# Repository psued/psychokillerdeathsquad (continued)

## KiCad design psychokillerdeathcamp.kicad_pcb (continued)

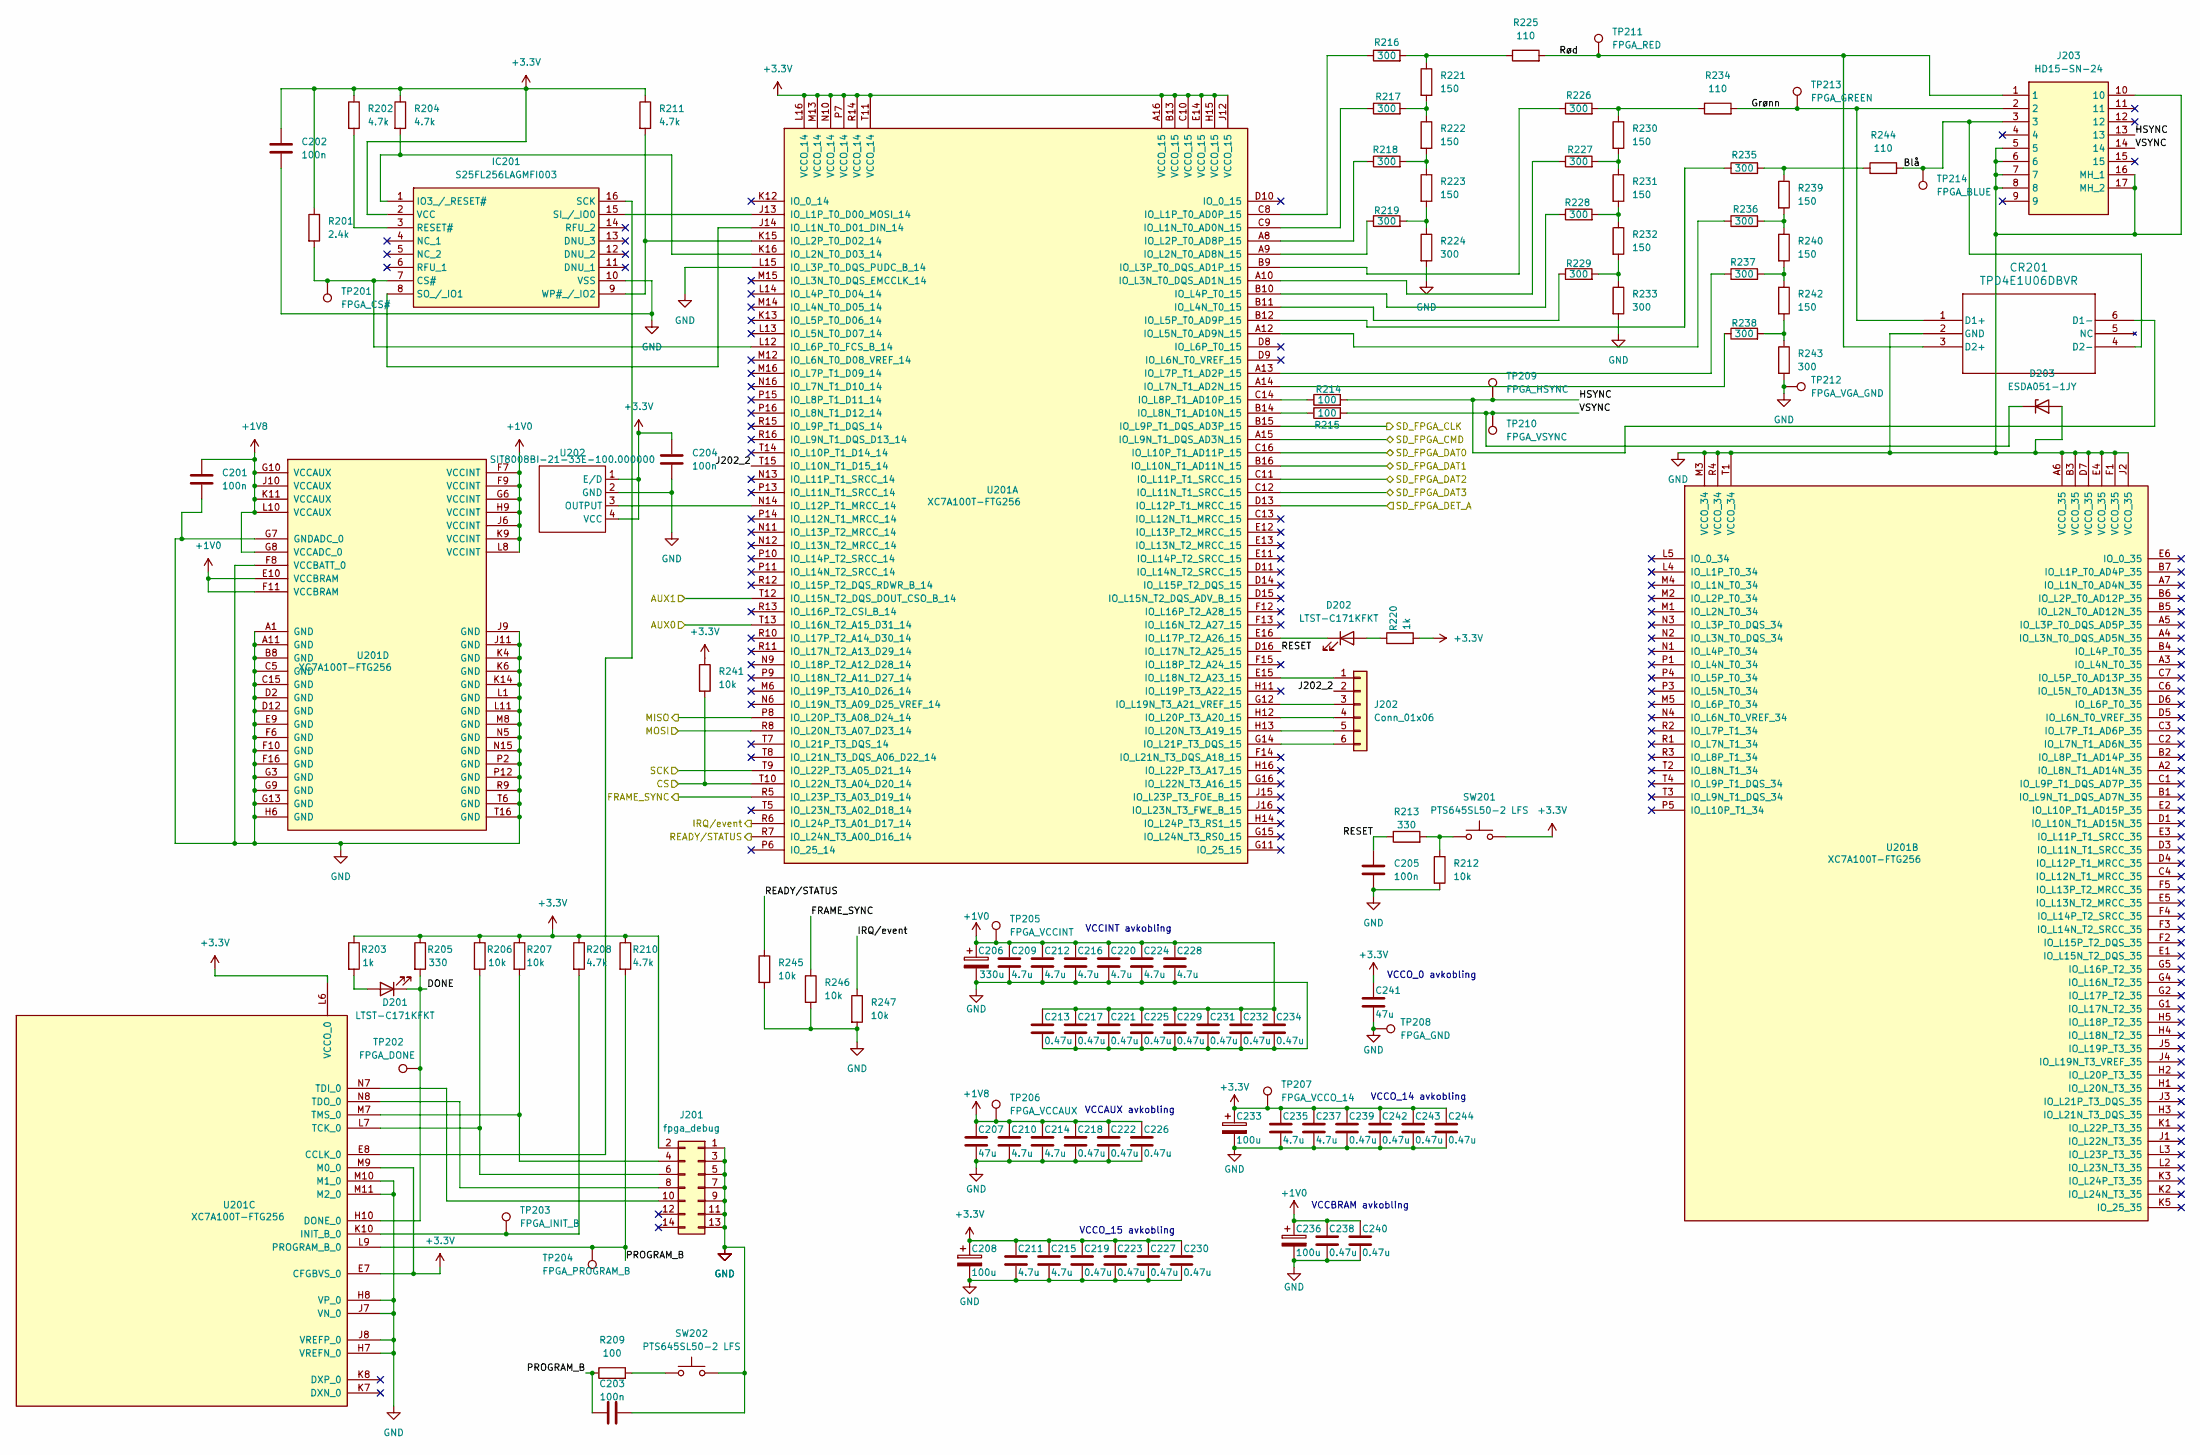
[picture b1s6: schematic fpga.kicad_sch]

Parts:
C201, C202, C203, C204, C205: 100n; C_0805_2012Metric_Pad1.18x1.45mm_HandSolder
C206: 330u; CP_EIA-7343-20_Kemet-V_HandSolder
C207, C241: 47u; C_1210_3225Metric_Pad1.33x2.70mm_HandSolder
C208, C233, C236: 100u; CP_EIA-3216-18_Kemet-A_HandSolder
C209, C210, C211, C212, C214, C215, C216, C220, C224, C228, C235, C237: 4.7u; C_0805_2012Metric_Pad1.18x1.45mm_HandSolder
C213, C217, C218, C219, C221, C222, C223, C225, C226, C227, C229, C230, C231, C232, C234, C238, C239, C240, C242, C243, C244: 0.47u; C_0805_2012Metric_Pad1.18x1.45mm_HandSolder
CR201: TPD4E1U06DBVR
D201, D202: LTST-C171KFKT; LED_0805_2012Metric_Pad1.15x1.40mm_HandSolder
D203: ESDA051-1JY; D_SOD-323_HandSoldering
IC201: S25FL256LAGMFI003; SOIC-16W_7.5x10.3mm_P1.27mm; Mouser Part Number 727-S25FL256LAGMFI03
J201: fpga_debug; SHDR14W55P200_2X7_1665X630X640P
J202: Conn_01x06; PinHeader_1x06_P2.54mm_Vertical
J203: HD15-SN-24; HD15SN24; Manufacturer_Part_Number HD15-SN-24
R201: 2.4k; R_0805_2012Metric_Pad1.20x1.40mm_HandSolder
R202, R204, R208, R210, R211: 4.7k; R_0805_2012Metric_Pad1.20x1.40mm_HandSolder
R203, R220: 1k; R_0805_2012Metric_Pad1.20x1.40mm_HandSolder
R205, R213: 330; R_0805_2012Metric_Pad1.20x1.40mm_HandSolder
R206, R207, R212, R241, R245, R246, R247: 10k; R_0805_2012Metric_Pad1.20x1.40mm_HandSolder
R209, R214, R215: 100; R_0805_2012Metric_Pad1.20x1.40mm_HandSolder
R216, R217, R218, R219, R224, R226, R227, R228, R229, R233, R235, R236, R237, R238, R243: 300; R_0805_2012Metric_Pad1.20x1.40mm_HandSolder
R221, R222, R223, R230, R231, R232, R239, R240, R242: 150; R_0805_2012Metric_Pad1.20x1.40mm_HandSolder
R225, R234, R244: 110; R_0805_2012Metric_Pad1.20x1.40mm_HandSolder
SW201, SW202: PTS645SL50-2 LFS; SW_PUSH_6mm_H5mm
TP201: FPGA_CS#; TestPoint_Pad_D1.5mm
TP202: FPGA_DONE; TestPoint_Pad_D1.5mm
TP203: FPGA_INIT_B; PinHeader_1x01_P2.54mm_Vertical
TP204: FPGA_PROGRAM_B; TestPoint_Pad_D1.5mm
TP205: FPGA_VCCINT; TestPoint_Pad_D1.5mm
TP206: FPGA_VCCAUX; TestPoint_Pad_D1.5mm
TP207: FPGA_VCCO_14; TestPoint_Pad_D1.5mm
TP208: FPGA_GND; PinHeader_1x01_P2.54mm_Vertical
TP209: FPGA_HSYNC; TestPoint_Pad_D1.5mm
TP210: FPGA_VSYNC; TestPoint_Pad_D1.5mm
TP211: FPGA_RED; TestPoint_Pad_D1.5mm
TP212: FPGA_VGA_GND; PinHeader_1x01_P2.54mm_Vertical
TP213: FPGA_GREEN; TestPoint_Pad_D1.5mm
TP214: FPGA_BLUE; TestPoint_Pad_D1.5mm
U201: XC7A100T-FTG256; BGA-256_17.0x17.0mm_Layout16x16_P1.0mm_Ball0.5mm_Pad0.4mm_N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
U202: SIT8008BI-21-33E-100.000000; OSC_SiT8008BI-21-33E-100.000000

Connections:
+1V0: C206.1, C209.1, C212.1, C213.1, C216.1, C217.1, C220.1, C221.1, C224.1, C225.1, C228.1, C229.1, C231.1, C232.1, C234.1, C236.1, C238.1, C240.1, TP205.1 (1_1), U201.E10 (VCCBRAM), U201.F7 (VCCINT), U201.F9 (VCCINT), U201.F11 (VCCBRAM), U201.G6 (VCCINT), U201.H9 (VCCINT), U201.J6 (VCCINT), U201.K9 (VCCINT), U201.L8 (VCCINT); also elsewhere on the board
+1V8: C201.1, C207.1, C210.1, C214.1, C218.1, C222.1, C226.1, TP206.1 (1_1), U201.G8 (VCCADC_0), U201.G10 (VCCAUX), U201.J10 (VCCAUX), U201.K11 (VCCAUX), U201.L10 (VCCAUX); also elsewhere on the board
+3.3V: C202.1, C204.1, C208.1, C211.1, C215.1, C219.1, C223.1, C227.1, C230.1, C233.1, C235.1, C237.1, C239.1, C241.1, C242.1, C243.1, C244.1, IC201.2 (VCC), J201.2, R201.1, R202.1, R203.1, R204.1, R205.1, R206.1, R207.1, R208.1, R210.1, R211.1, R220.2, R241.1, SW201.2, TP207.1 (1_1), U201.A16 (VCCO_15), U201.B13 (VCCO_15), U201.C10 (VCCO_15), U201.E7 (CFGBVS_0), U201.E14 (VCCO_15), U201.H15 (VCCO_15), U201.J12 (VCCO_15), U201.L6 (VCCO_0), U201.L16 (VCCO_14), U201.M9 (M0_0), U201.M13 (VCCO_14), U201.N10 (VCCO_14), U201.P7 (VCCO_14), U201.R14 (VCCO_14), U201.T11 (VCCO_14), U202.1 (E/D), U202.4 (VCC); also elsewhere on the board
/MCU/AUX0: U201.T13 (IO_L16N_T2_A15_D31_14); also elsewhere on the board
/MCU/AUX1: U201.T12 (IO_L15N_T2_DQS_DOUT_CSO_B_14); also elsewhere on the board
/MCU/CS: R241.2, U201.T10 (IO_L22N_T3_A04_D20_14); also elsewhere on the board
/MCU/MISO: U201.P8 (IO_L20P_T3_A08_D24_14); also elsewhere on the board
/MCU/MOSI: U201.R8 (IO_L20N_T3_A07_D23_14); also elsewhere on the board
/MCU/SCK: U201.T9 (IO_L22P_T3_A05_D21_14); also elsewhere on the board
/SD cards/SD_FPGA_CLK: U201.B15 (IO_L9P_T1_DQS_AD3P_15); also elsewhere on the board
/SD cards/SD_FPGA_CMD: U201.A15 (IO_L9N_T1_DQS_AD3N_15); also elsewhere on the board
/SD cards/SD_FPGA_DAT0: U201.C16 (IO_L10P_T1_AD11P_15); also elsewhere on the board
/SD cards/SD_FPGA_DAT1: U201.B16 (IO_L10N_T1_AD11N_15); also elsewhere on the board
/SD cards/SD_FPGA_DAT2: U201.C11 (IO_L11P_T1_SRCC_15); also elsewhere on the board
/SD cards/SD_FPGA_DAT3: U201.C12 (IO_L11N_T1_SRCC_15); also elsewhere on the board
/SD cards/SD_FPGA_DET_A: U201.D13 (IO_L12P_T1_MRCC_15); also elsewhere on the board
/fpga/Blå: CR201.4 (D2-), J203.3, R244.2, TP214.1 (1_1)
/fpga/DONE: D201.1 (K), R205.2, TP202.1 (1_1), U201.H10 (DONE_0)
/fpga/FRAME_SYNC: R246.1, U201.R5 (IO_L23P_T3_A03_D19_14); also elsewhere on the board
/fpga/Grønn: CR201.1 (D1+), J203.2, R234.2, TP213.1 (1_1)
/fpga/HSYNC: CR201.6 (D1-), J203.13, R214.2, TP209.1 (1_1)
/fpga/IRQ/event: R247.1, U201.R6 (IO_L24P_T3_A01_D17_14); also elsewhere on the board
/fpga/J202_2: J202.2, U201.T15 (IO_L10N_T1_D15_14)
/fpga/PROGRAM_B: C203.2, R209.1, R210.2, TP204.1 (1_1), U201.L9 (PROGRAM_B_0)
/fpga/READY/STATUS: R245.1, U201.R7 (IO_L24N_T3_A00_D16_14); also elsewhere on the board
/fpga/RESET: C205.1, R213.1, U201.D16 (IO_L17N_T2_A25_15)
/fpga/Rød: CR201.3 (D2+), J203.1, R225.2, TP211.1 (1_1)
/fpga/VSYNC: D203.1 (K), J203.14, R215.2, TP210.1 (1_1)
GND: C201.2, C202.2, C203.1, C204.2, C205.2, C206.2, C207.2, C208.2, C209.2, C210.2, C211.2, C212.2, C213.2, C214.2, C215.2, C216.2, C217.2, C218.2, C219.2, C220.2, C221.2, C222.2, C223.2, C224.2, C225.2, C226.2, C227.2, C228.2, C229.2, C230.2, C231.2, C232.2, C233.2, C234.2, C235.2, C236.2, C237.2, C238.2, C239.2, C240.2, C241.2, C242.2, C243.2, C244.2, CR201.2 (GND), D203.2 (A), IC201.10 (VSS), J201.1, J201.3, J201.5, J201.7, J201.9, J201.11, J201.13, J203.5, J203.6, J203.7, J203.8, J203.10, J203.16 (MH_1), J203.17 (MH_2), R212.2, R224.2, R233.2, R243.2, R245.2, R246.2, R247.2, SW202.2, TP208.1 (1_1), TP212.1 (1_1), U201.A1 (GND), U201.A6 (VCCO_35), U201.A11 (GND), U201.B3 (VCCO_35), U201.B8 (GND), U201.C5 (GND), U201.C15 (GND), U201.D2 (GND), U201.D7 (VCCO_35), U201.D12 (GND), U201.E4 (VCCO_35), U201.E9 (GND), U201.F1 (VCCO_35), U201.F6 (GND), U201.F8 (VCCBATT_0), U201.F10 (GND), U201.F16 (GND), U201.G3 (GND), U201.G7 (GNDADC_0), U201.G9 (GND), U201.G13 (GND), U201.H6 (GND), U201.H7 (VREFN_0), U201.H8 (VP_0), U201.J2 (VCCO_35), U201.J7 (VN_0), U201.J8 (VREFP_0), U201.J9 (GND), U201.J11 (GND), U201.K4 (GND), U201.K6 (GND), U201.K14 (GND), U201.L1 (GND), U201.L11 (GND), U201.L15 (IO_L3P_T0_DQS_PUDC_B_14), U201.M3 (VCCO_34), U201.M8 (GND), U201.M10 (M1_0), U201.M11 (M2_0), U201.N5 (GND), U201.N15 (GND), U201.P2 (GND), U201.P12 (GND), U201.R4 (VCCO_34), U201.R9 (GND), U201.T1 (VCCO_34), U201.T6 (GND), U201.T16 (GND), U202.2 (GND); also elsewhere on the board
unnamed: D201.2 (A), R203.2
unnamed: D202.2 (A), R220.1
unnamed: D202.1 (K), U201.E16 (IO_L17P_T2_A26_15)
unnamed: IC201.7 (CS#), R201.2, TP201.1 (1_1), U201.L12 (IO_L6P_T0_FCS_B_14)
unnamed: IC201.1 (IO3_/_RESET#), R204.2, U201.K16 (IO_L2N_T0_D03_14)
unnamed: IC201.3 (RESET#), R202.2
unnamed: IC201.16 (SCK), U201.E8 (CCLK_0)
unnamed: IC201.15 (SI_/_IO0), U201.J13 (IO_L1P_T0_D00_MOSI_14)
unnamed: IC201.8 (SO_/_IO1), U201.J14 (IO_L1N_T0_D01_DIN_14)
unnamed: IC201.9 (WP#_/_IO2), R211.2, U201.K15 (IO_L2P_T0_D02_14)
unnamed: J201.4, R207.2, U201.M7 (TMS_0)
unnamed: J201.6, R206.2, U201.L7 (TCK_0)
unnamed: J201.8, U201.N8 (TDO_0)
unnamed: J201.10, U201.N7 (TDI_0)
unnamed: J202.1, U201.E15 (IO_L18N_T2_A23_15)
unnamed: J202.3, U201.G12 (IO_L19N_T3_A21_VREF_15)
unnamed: J202.4, U201.H12 (IO_L20P_T3_A20_15)
unnamed: J202.5, U201.H13 (IO_L20N_T3_A19_15)
unnamed: J202.6, U201.G14 (IO_L21P_T3_DQS_15)
unnamed: R209.2, SW202.1
unnamed: R212.1, R213.2, SW201.1
unnamed: R216.2, R221.1, R225.1
unnamed: R217.2, R221.2, R222.1
unnamed: R218.2, R222.2, R223.1
unnamed: R219.2, R223.2, R224.1
unnamed: R226.2, R230.1, R234.1
unnamed: R227.2, R230.2, R231.1
unnamed: R228.2, R231.2, R232.1
unnamed: R229.2, R232.2, R233.1
unnamed: R235.2, R239.1, R244.1
unnamed: R236.2, R239.2, R240.1
unnamed: R237.2, R240.2, R242.1
unnamed: R238.2, R242.2, R243.1
unnamed: R217.1, U201.C9 (IO_L1N_T0_AD0N_15)
unnamed: R216.1, U201.C8 (IO_L1P_T0_AD0P_15)
unnamed: R219.1, U201.A9 (IO_L2N_T0_AD8N_15)
unnamed: R218.1, U201.A8 (IO_L2P_T0_AD8P_15)
unnamed: R227.1, U201.A10 (IO_L3N_T0_DQS_AD1N_15)
unnamed: R226.1, U201.B9 (IO_L3P_T0_DQS_AD1P_15)
unnamed: R229.1, U201.B11 (IO_L4N_T0_15)
unnamed: R228.1, U201.B10 (IO_L4P_T0_15)
unnamed: R236.1, U201.A12 (IO_L5N_T0_AD9N_15)
unnamed: R235.1, U201.B12 (IO_L5P_T0_AD9P_15)
unnamed: R238.1, U201.A14 (IO_L7N_T1_AD2N_15)
unnamed: R237.1, U201.A13 (IO_L7P_T1_AD2P_15)
unnamed: R215.1, U201.B14 (IO_L8N_T1_AD10N_15)
unnamed: R214.1, U201.C14 (IO_L8P_T1_AD10P_15)
unnamed: U201.N14 (IO_L12P_T1_MRCC_14), U202.3 (OUTPUT)
unnamed: R208.2, TP203.1 (1_1), U201.K10 (INIT_B_0)

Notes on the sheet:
VCCAUX avkobling
VCCO_15 avkobling
VCCO_0 avkobling
VCCBRAM avkobling
VCCO_14 avkobling
VCCINT avkobling

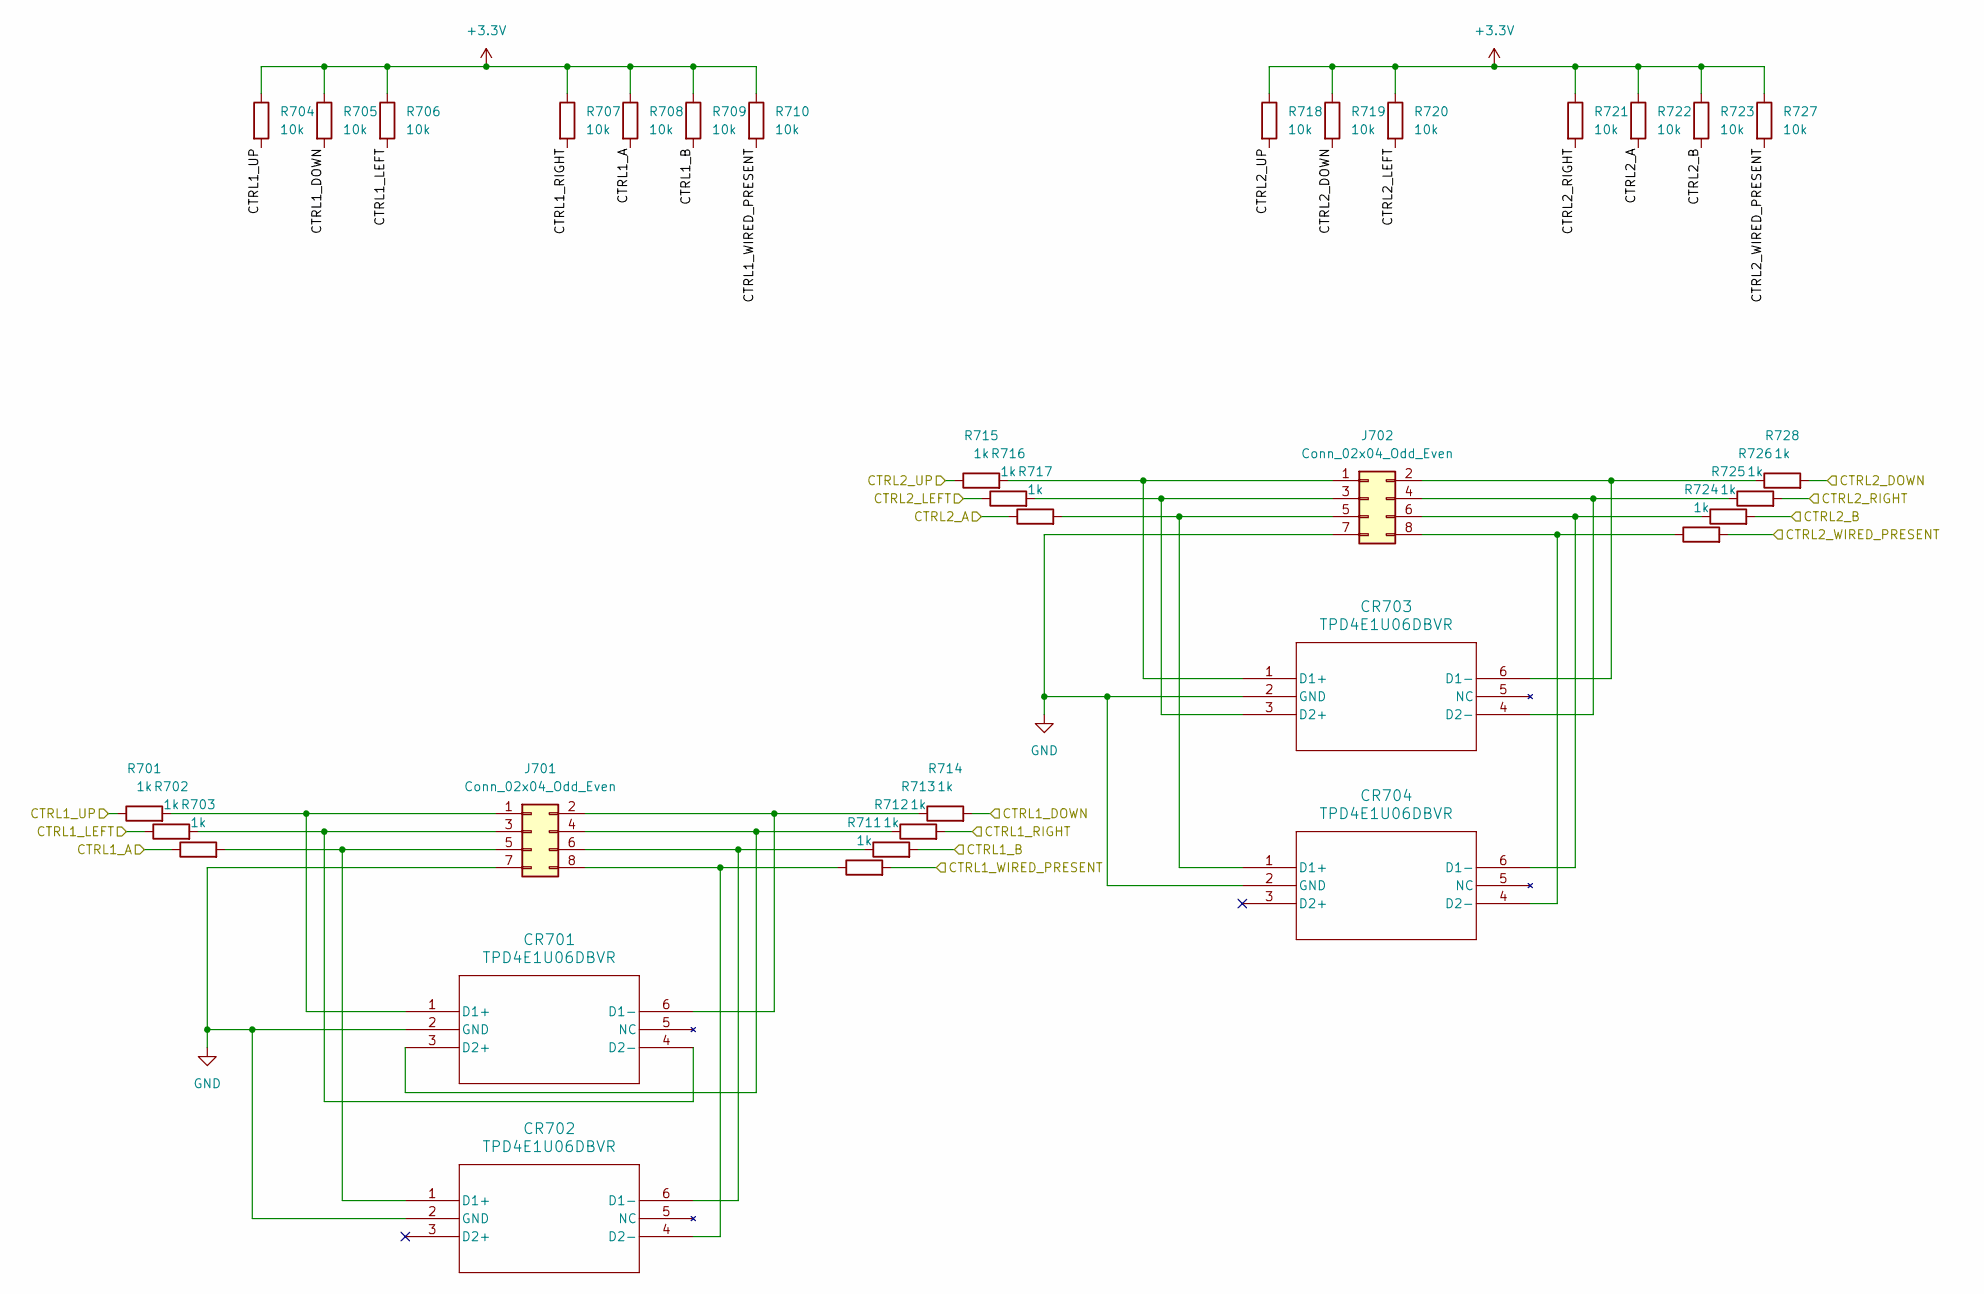
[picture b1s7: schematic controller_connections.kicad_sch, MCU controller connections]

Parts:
CR701, CR702, CR703, CR704: TPD4E1U06DBVR
J701, J702: Conn_02x04_Odd_Even; Molex_Micro-Fit_3.0_43045-0800_2x04_P3.00mm_Horizontal
R701, R702, R703, R711, R712, R713, R714, R715, R716, R717, R724, R725, R726, R728: 1k; R_0805_2012Metric_Pad1.20x1.40mm_HandSolder
R704, R705, R706, R707, R708, R709, R710, R718, R719, R720, R721, R722, R723, R727: 10k; R_0805_2012Metric_Pad1.20x1.40mm_HandSolder

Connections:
+3.3V: R704.1, R705.1, R706.1, R707.1, R708.1, R709.1, R710.1, R718.1, R719.1, R720.1, R721.1, R722.1, R723.1, R727.1; also elsewhere on the board
/MCU/Controller connections/CTRL1_A: R703.1, R708.2; also elsewhere on the board
/MCU/Controller connections/CTRL1_B: R709.2, R712.2; also elsewhere on the board
/MCU/Controller connections/CTRL1_DOWN: R705.2, R714.2; also elsewhere on the board
/MCU/Controller connections/CTRL1_LEFT: R702.1, R706.2; also elsewhere on the board
/MCU/Controller connections/CTRL1_RIGHT: R707.2, R713.2; also elsewhere on the board
/MCU/Controller connections/CTRL1_UP: R701.1, R704.2; also elsewhere on the board
/MCU/Controller connections/CTRL1_WIRED_PRESENT: R710.2, R711.2; also elsewhere on the board
/MCU/Controller connections/CTRL2_A: R717.1, R722.2; also elsewhere on the board
/MCU/Controller connections/CTRL2_B: R723.2, R725.2; also elsewhere on the board
/MCU/Controller connections/CTRL2_DOWN: R719.2, R728.2; also elsewhere on the board
/MCU/Controller connections/CTRL2_LEFT: R716.1, R720.2; also elsewhere on the board
/MCU/Controller connections/CTRL2_RIGHT: R721.2, R726.2; also elsewhere on the board
/MCU/Controller connections/CTRL2_UP: R715.1, R718.2; also elsewhere on the board
/MCU/Controller connections/CTRL2_WIRED_PRESENT: R724.2, R727.2; also elsewhere on the board
GND: CR701.2 (GND), CR702.2 (GND), CR703.2 (GND), CR704.2 (GND), J701.7, J702.7; also elsewhere on the board
unnamed: CR701.1 (D1+), J701.1, R701.2
unnamed: CR701.6 (D1-), J701.2, R714.1
unnamed: CR701.3 (D2+), J701.4, R713.1
unnamed: CR701.4 (D2-), J701.3, R702.2
unnamed: CR702.1 (D1+), J701.5, R703.2
unnamed: CR702.6 (D1-), J701.6, R712.1
unnamed: CR702.4 (D2-), J701.8, R711.1
unnamed: CR703.1 (D1+), J702.1, R715.2
unnamed: CR703.6 (D1-), J702.2, R728.1
unnamed: CR703.3 (D2+), J702.3, R716.2
unnamed: CR703.4 (D2-), J702.4, R726.1
unnamed: CR704.1 (D1+), J702.5, R717.2
unnamed: CR704.6 (D1-), J702.6, R725.1
unnamed: CR704.4 (D2-), J702.8, R724.1

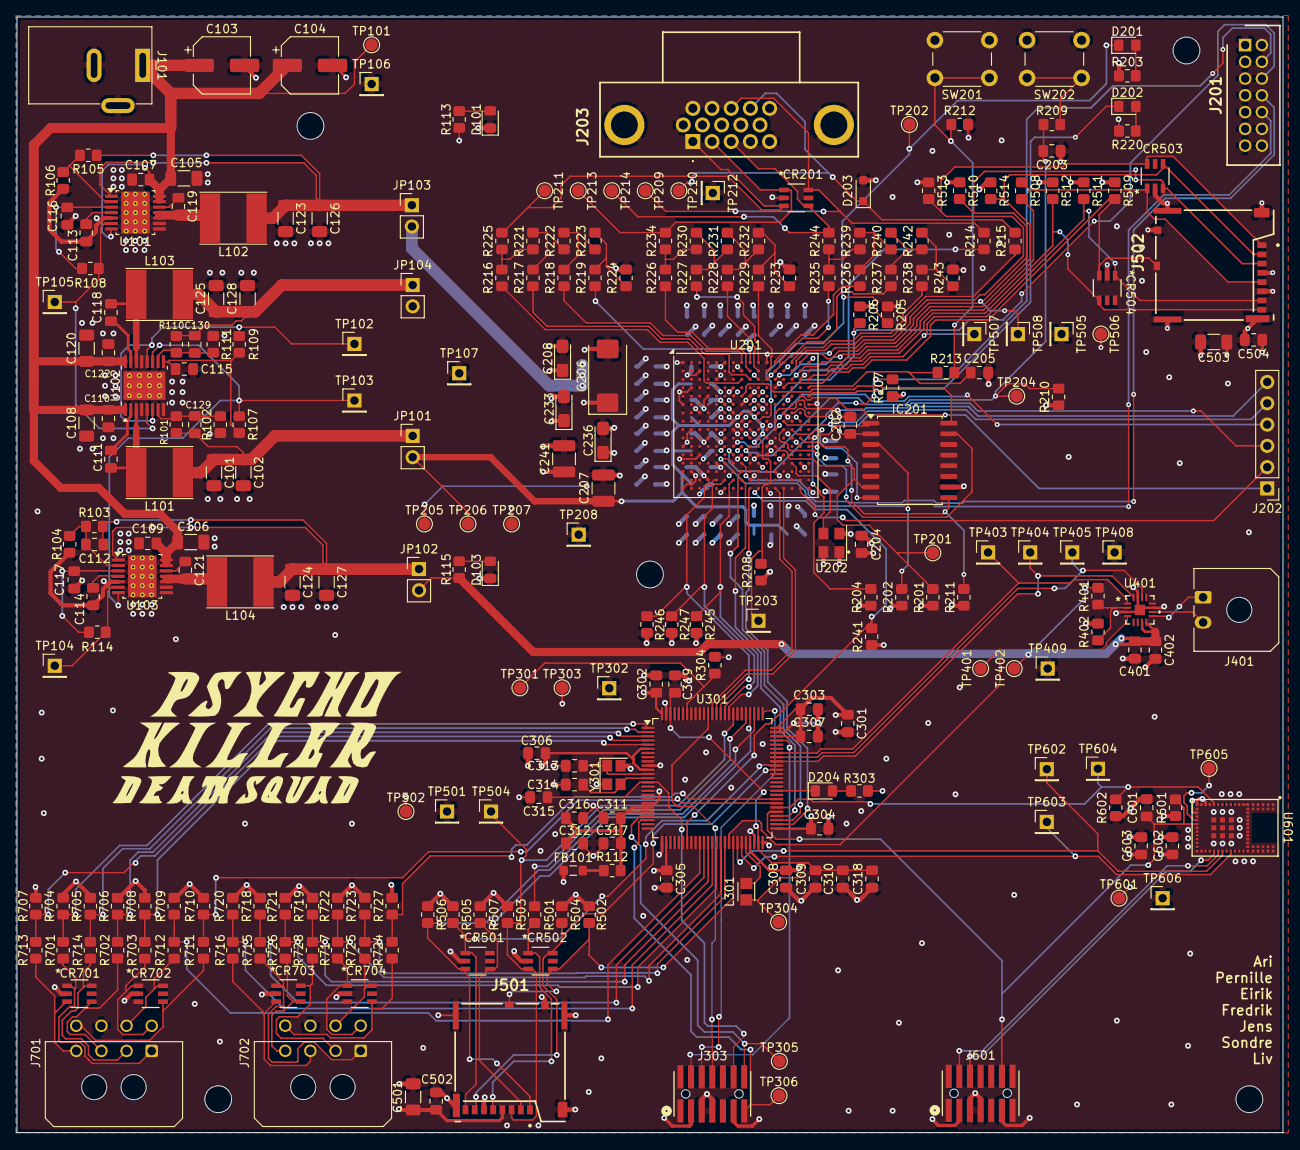
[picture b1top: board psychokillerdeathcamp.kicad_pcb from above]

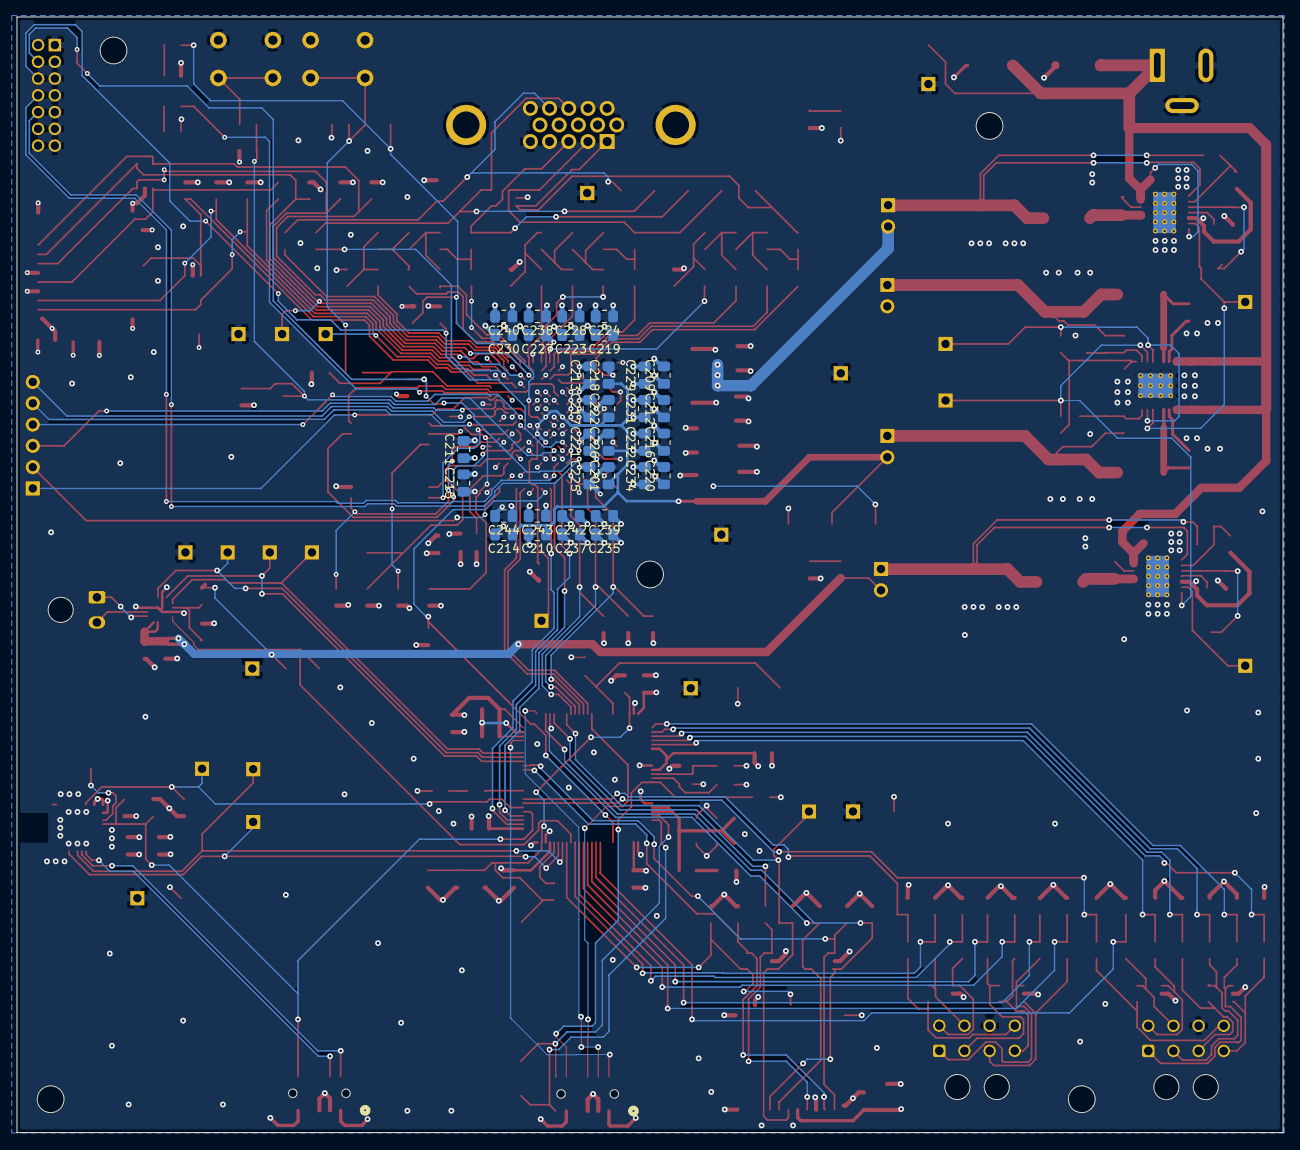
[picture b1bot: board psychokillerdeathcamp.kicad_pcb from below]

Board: 4 copper layers, 151.0 x 133.1 mm, 312 parts (34 on the bottom side), 174 nets.

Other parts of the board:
BL: MountingHole_3.2mm_M3
BR: MountingHole_3.2mm_M3
M: MountingHole_3.2mm_M3
TL: MountingHole_3.2mm_M3
TR: MountingHole_3.2mm_M3

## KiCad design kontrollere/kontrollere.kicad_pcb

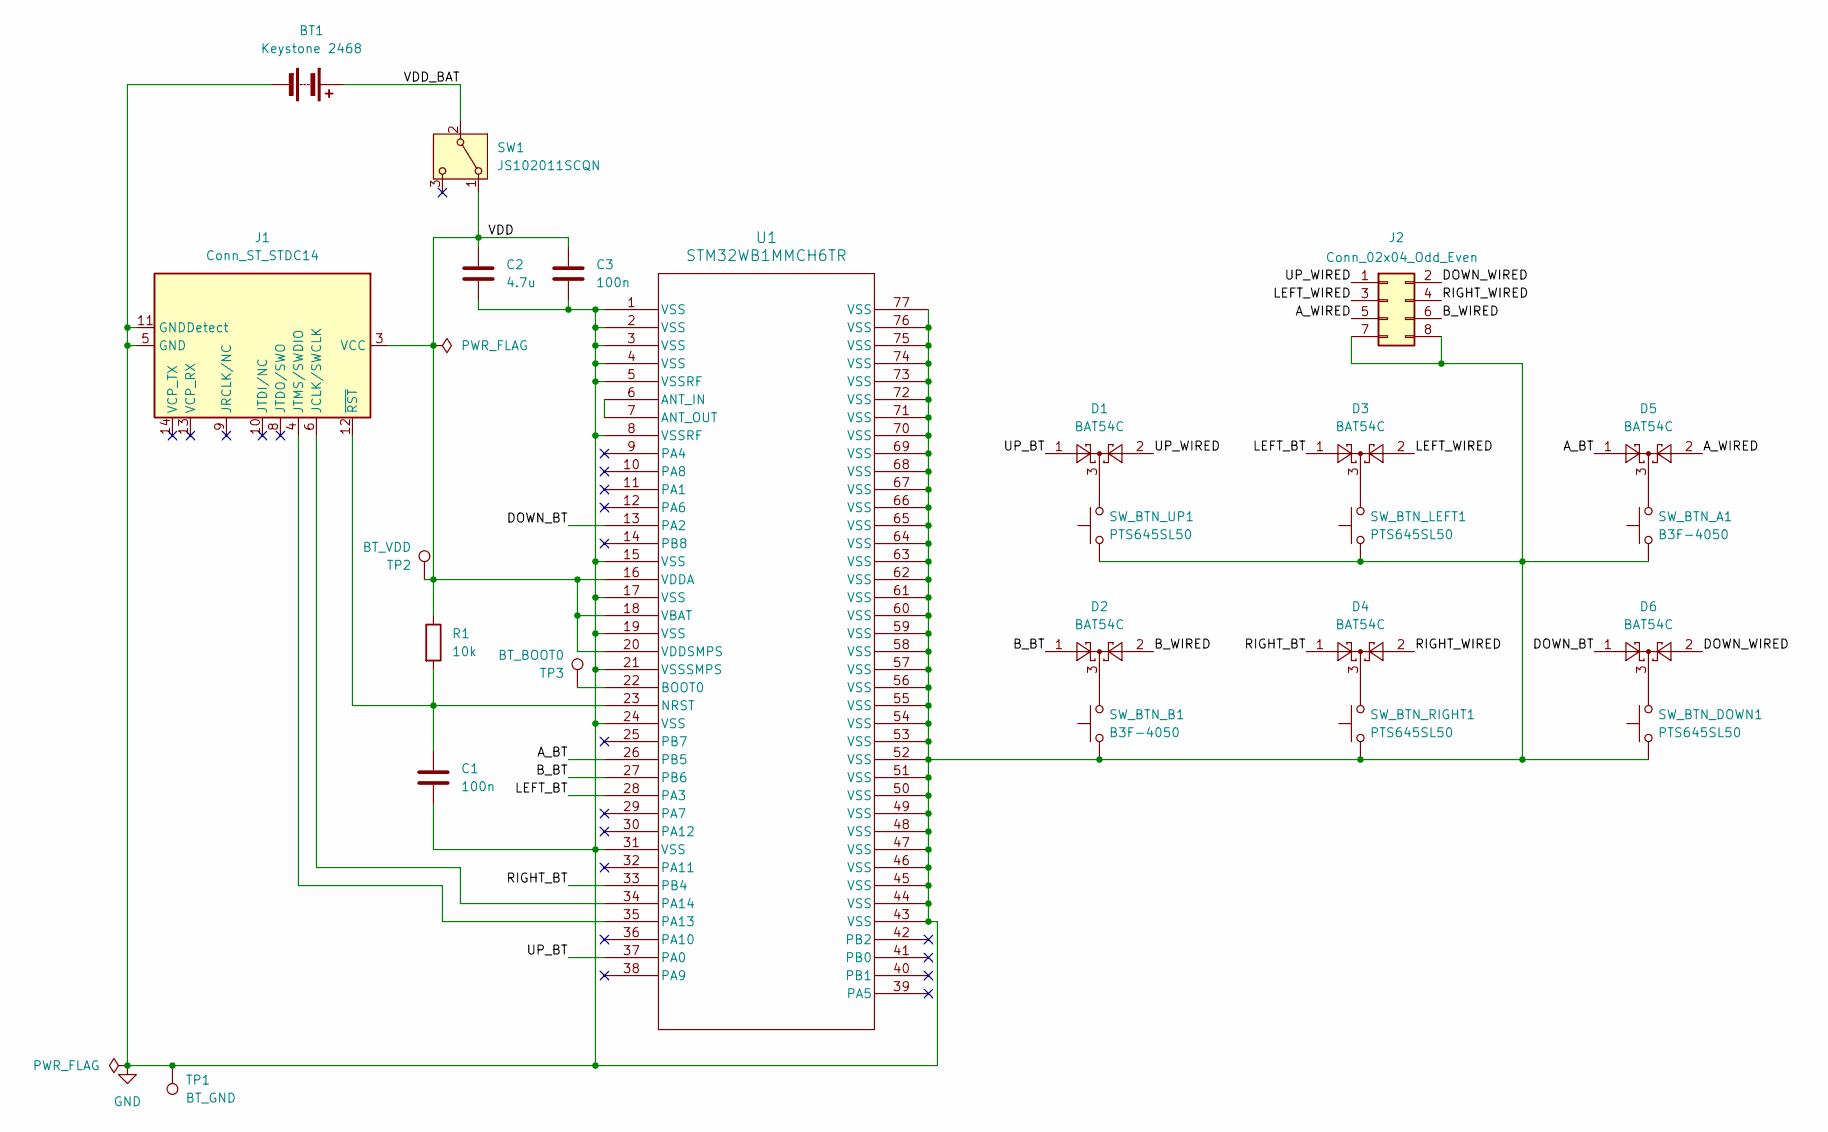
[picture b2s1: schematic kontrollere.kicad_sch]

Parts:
BT1: Keystone 2468; BatteryHolder_Keystone_2468_2xAAA
C1, C3: 100n; C_0805_2012Metric_Pad1.18x1.45mm_HandSolder
C2: 4.7u; C_0805_2012Metric_Pad1.18x1.45mm_HandSolder
D1, D2, D3, D4, D5, D6: BAT54C; SOT-23_Handsoldering
J1: Conn_ST_STDC14; CONN_FTSH-x07-01-x-DV-K-A_SAI
J2: Conn_02x04_Odd_Even; Molex_Micro-Fit_3.0_43045-0800_2x04_P3.00mm_Horizontal
R1: 10k; R_0805_2012Metric_Pad1.20x1.40mm_HandSolder
SW1: JS102011SCQN; SWITCH_1SCQN
SW_BTN_A1: B3F-4050; SW_SPST_Omron_B3F-40xx
SW_BTN_B1: B3F-4050; SW_SPST_Omron_B3F-40xx
SW_BTN_DOWN1: PTS645SL50; SW_PUSH_6mm_H5mm
SW_BTN_LEFT1: PTS645SL50; SW_PUSH_6mm_H5mm
SW_BTN_RIGHT1: PTS645SL50; SW_PUSH_6mm_H5mm
SW_BTN_UP1: PTS645SL50; SW_PUSH_6mm_H5mm
TP1: BT_GND; TestPoint_Pad_D1.5mm
TP2: BT_VDD; TestPoint_Pad_D1.5mm
TP3: BT_BOOT0; TestPoint_Pad_D1.5mm
U1: STM32WB1MMCH6TR; LGA77_6P5X10_STM

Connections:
/A_BT: D5.1, U1.26 (PB5)
/A_WIRED: D5.2, J2.5
/B_BT: D2.1, U1.27 (PB6)
/B_WIRED: D2.2, J2.6
/DOWN_BT: D6.1, U1.13 (PA2)
/DOWN_WIRED: D6.2, J2.2
/LEFT_BT: D3.1, U1.28 (PA3)
/LEFT_WIRED: D3.2, J2.3
/RIGHT_BT: D4.1, U1.33 (PB4)
/RIGHT_WIRED: D4.2, J2.4
/UP_BT: D1.1, U1.37 (PA0)
/UP_WIRED: D1.2, J2.1
/VDD: C2.1, C3.1, J1.3 (VCC), R1.1, SW1.1 (A), TP2.1 (1_1), U1.16 (VDDA), U1.18 (VBAT), U1.20 (VDDSMPS)
/VDD_BAT: BT1.1 (+), SW1.2 (B)
GND: BT1.2 (-), C1.2, C2.2, C3.2, J1.5 (GND), J1.7 (GND), J1.11 (GNDDetect), J2.7, J2.8, SW_BTN_A1.1, SW_BTN_B1.1, SW_BTN_DOWN1.1, SW_BTN_LEFT1.1, SW_BTN_RIGHT1.1, SW_BTN_UP1.1, TP1.1 (1_1), U1.1 (VSS), U1.2 (VSS), U1.3 (VSS), U1.4 (VSS), U1.5 (VSSRF), U1.8 (VSSRF), U1.15 (VSS), U1.17 (VSS), U1.19 (VSS), U1.21 (VSSSMPS), U1.24 (VSS), U1.31 (VSS), U1.43 (VSS), U1.44 (VSS), U1.45 (VSS), U1.46 (VSS), U1.47 (VSS), U1.48 (VSS), U1.49 (VSS), U1.50 (VSS), U1.51 (VSS), U1.52 (VSS), U1.53 (VSS), U1.54 (VSS), U1.55 (VSS), U1.56 (VSS), U1.57 (VSS), U1.58 (VSS), U1.59 (VSS), U1.60 (VSS), U1.61 (VSS), U1.62 (VSS), U1.63 (VSS), U1.64 (VSS), U1.65 (VSS), U1.66 (VSS), U1.67 (VSS), U1.68 (VSS), U1.69 (VSS), U1.70 (VSS), U1.71 (VSS), U1.72 (VSS), U1.73 (VSS), U1.74 (VSS), U1.75 (VSS), U1.76 (VSS), U1.77 (VSS)
unnamed: D1.3, SW_BTN_UP1.2
unnamed: D2.3, SW_BTN_B1.2
unnamed: D3.3, SW_BTN_LEFT1.2
unnamed: D4.3, SW_BTN_RIGHT1.2
unnamed: D5.3, SW_BTN_A1.2
unnamed: D6.3, SW_BTN_DOWN1.2
unnamed: J1.6 (JCLK/SWCLK), U1.34 (PA14)
unnamed: J1.4 (JTMS/SWDIO), U1.35 (PA13)
unnamed: C1.1, J1.12 (~RST), R1.2, U1.23 (NRST)
unnamed: U1.6 (ANT_IN), U1.7 (ANT_OUT)
unnamed: TP3.1 (1_1), U1.22 (BOOT0)

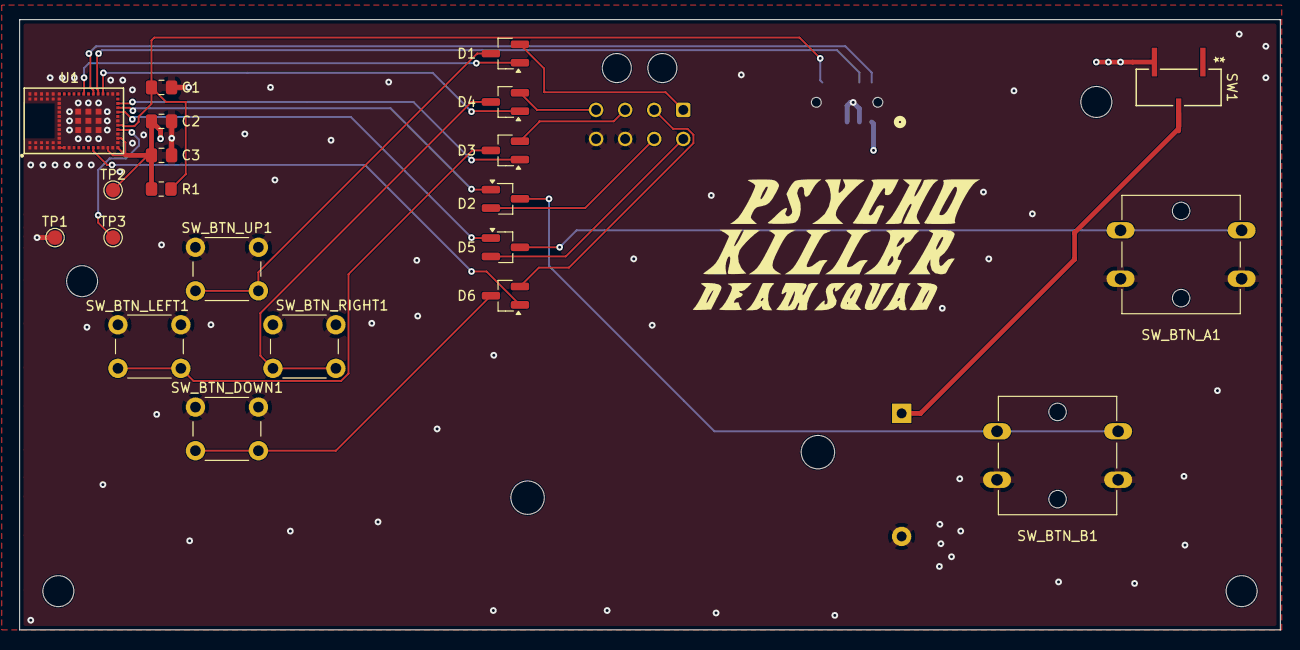
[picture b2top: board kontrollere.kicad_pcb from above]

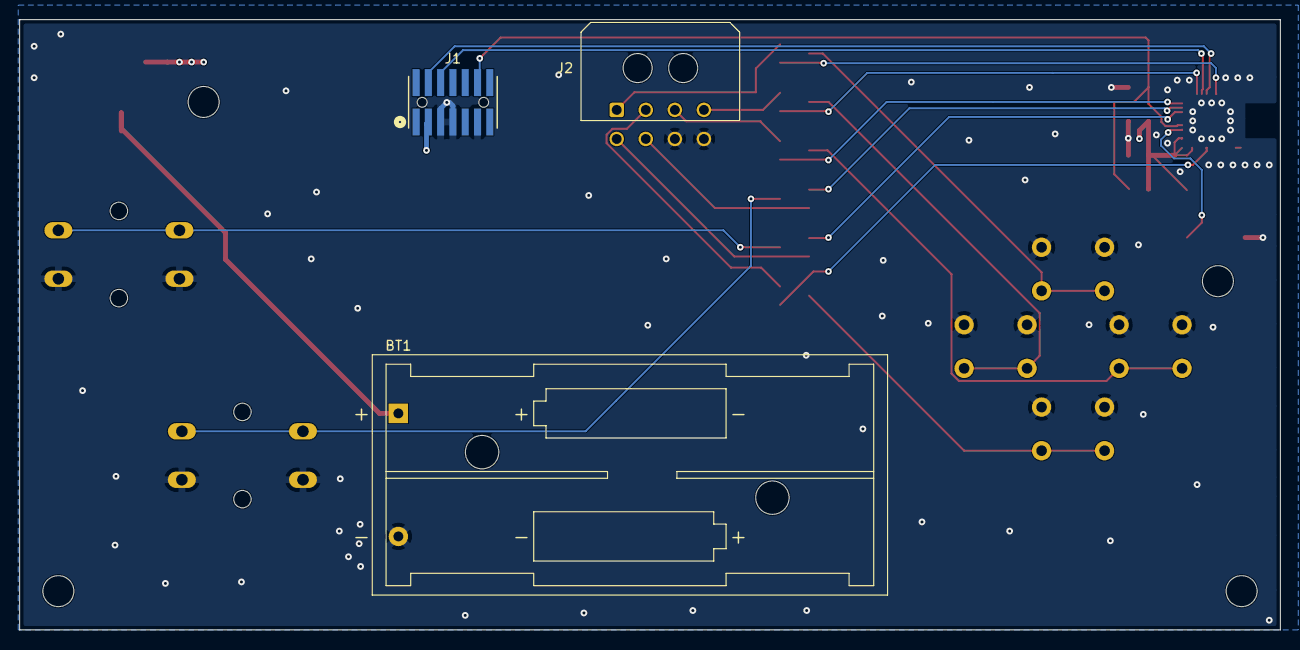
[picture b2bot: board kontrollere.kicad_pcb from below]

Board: 4 copper layers, 130.2 x 63.0 mm, 28 parts (3 on the bottom side), 26 nets.

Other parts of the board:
BL: MountingHole_3.2mm_M3
BR: MountingHole_3.2mm_M3
L: MountingHole_3.2mm_M3
TR: MountingHole_3.2mm_M3

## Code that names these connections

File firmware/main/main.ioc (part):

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Mcu.Name=STM32U545VETxQ
Mcu.Package=LQFP100
Mcu.UserName=STM32U545VETxQ
PA0.Mode=Asynchronous
PA0.Signal=UART4_TX
PA1.Mode=Asynchronous
PA1.Signal=UART4_RX
PA10.Mode=SAI_A_Master
PA10.Signal=SAI1_SD_A
PA8.Mode=SAI_A_Master
PA8.Signal=SAI1_SCK_A
PA9.Mode=SAI_A_Master
PA9.Signal=SAI1_FS_A
PB0.GPIOParameters=PinState,GPIO_Label
PB0.GPIO_Label=FPGA_CS
PB0.PinState=GPIO_PIN_SET
PB0.Signal=GPIO_Output
PB10.Mode=Asynchronous
PB10.Signal=USART3_TX
PB11.Mode=Asynchronous
PB11.Signal=USART3_RX
PB13.GPIOParameters=GPIO_Speed
PB13.GPIO_Speed=GPIO_SPEED_FREQ_MEDIUM
PB13.Mode=Full_Duplex_Master
PB13.Signal=SPI2_SCK
PB14.GPIOParameters=GPIO_Speed
PB14.GPIO_Speed=GPIO_SPEED_FREQ_MEDIUM
PB14.Mode=Full_Duplex_Master
PB14.Signal=SPI2_MISO
PB15.GPIOParameters=GPIO_Speed
PB15.GPIO_Speed=GPIO_SPEED_FREQ_MEDIUM
PB15.Mode=Full_Duplex_Master
PB15.Signal=SPI2_MOSI
PC10.Mode=SD_4_bits_Wide_bus
PC10.Signal=SDMMC1_D2
PC11.Mode=SD_4_bits_Wide_bus
PC11.Signal=SDMMC1_D3
PC12.Mode=SD_4_bits_Wide_bus
PC12.Signal=SDMMC1_CK
PC8.Mode=SD_4_bits_Wide_bus
PC8.Signal=SDMMC1_D0
PC9.Mode=SD_4_bits_Wide_bus
PC9.Signal=SDMMC1_D1
PD10.GPIOParameters=GPIO_PuPd,GPIO_Label
PD10.GPIO_Label=P1_WIRED_PRESENT
PD10.GPIO_PuPd=GPIO_PULLUP
PD10.Signal=GPIO_Input
PD11.GPIOParameters=GPIO_PuPd,GPIO_Label
PD11.GPIO_Label=P2_WIRED_PRESENT
PD11.GPIO_PuPd=GPIO_PULLUP
PD11.Signal=GPIO_Input
PD13.GPIOParameters=PinState,GPIO_Label
PD13.GPIO_Label=HEARTBEAT_LED
PD13.PinState=GPIO_PIN_RESET
PD13.Signal=GPIO_Output
PD2.Mode=SD_4_bits_Wide_bus
PD2.Signal=SDMMC1_CMD
PD3.GPIOParameters=GPIO_Label
PD3.GPIO_Label=FPGA_READY
PD3.Signal=GPIO_Input
PD4.GPIOParameters=GPIO_Label,GPIO_ModeDefaultEXTI
PD4.GPIO_Label=FPGA_IRQ
PD4.GPIO_ModeDefaultEXTI=GPIO_MODE_IT_RISING
PD4.Signal=GPXTI4
PD5.GPIOParameters=GPIO_Label,GPIO_ModeDefaultEXTI
PD5.GPIO_Label=FPGA_FRAME
PD5.GPIO_ModeDefaultEXTI=GPIO_MODE_IT_RISING
PD5.Signal=GPXTI5
PD6.GPIOParameters=GPIO_Label
PD6.GPIO_Label=FPGA_AUX0
PD6.Signal=GPIO_Output
PD7.GPIOParameters=GPIO_Label
PD7.GPIO_Label=FPGA_AUX1
PD7.Signal=GPIO_Output
PD8.GPIOParameters=PinState,GPIO_PuPd,GPIO_Label,GPIO_ModeDefaultOutputPP
PD8.GPIO_Label=WB_NRST
PD8.GPIO_ModeDefaultOutputPP=GPIO_MODE_OUTPUT_OD
PD8.GPIO_PuPd=GPIO_NOPULL
PD8.PinState=GPIO_PIN_SET
PD8.Signal=GPIO_Output
PD9.GPIOParameters=GPIO_Label,GPIO_ModeDefaultEXTI
PD9.GPIO_Label=WB_HOST_IRQ
PD9.GPIO_ModeDefaultEXTI=GPIO_MODE_IT_RISING
PD9.Signal=GPXTI9
PE10.GPIOParameters=GPIO_PuPd,GPIO_Label
PE10.GPIO_Label=P2_LEFT
PE10.GPIO_PuPd=GPIO_PULLUP
PE10.Signal=GPIO_Input
PE11.GPIOParameters=GPIO_PuPd,GPIO_Label
PE11.GPIO_Label=P2_RIGHT
PE11.GPIO_PuPd=GPIO_PULLUP
PE11.Signal=GPIO_Input
PE12.GPIOParameters=GPIO_PuPd,GPIO_Label
PE12.GPIO_Label=P2_A
PE12.GPIO_PuPd=GPIO_PULLUP
PE12.Signal=GPIO_Input
PE13.GPIOParameters=GPIO_PuPd,GPIO_Label
PE13.GPIO_Label=P2_B
PE13.GPIO_PuPd=GPIO_PULLUP
PE13.Signal=GPIO_Input
PE14.GPIOParameters=GPIO_Label
PE14.GPIO_Label=AUDIO_EN
PE14.Signal=GPIO_Output
PE15.GPIOParameters=GPIO_PuPd,GPIO_Label
PE15.GPIO_Label=SD_DETECT
PE15.GPIO_PuPd=GPIO_NOPULL
PE15.Signal=GPIO_Input
PE2.GPIOParameters=GPIO_PuPd,GPIO_Label
PE2.GPIO_Label=P1_UP
PE2.GPIO_PuPd=GPIO_PULLUP
PE2.Signal=GPIO_Input
PE3.GPIOParameters=GPIO_PuPd,GPIO_Label
PE3.GPIO_Label=P1_DOWN
PE3.GPIO_PuPd=GPIO_PULLUP
PE3.Signal=GPIO_Input
PE4.GPIOParameters=GPIO_PuPd,GPIO_Label
PE4.GPIO_Label=P1_LEFT
PE4.GPIO_PuPd=GPIO_PULLUP
PE4.Signal=GPIO_Input
PE5.GPIOParameters=GPIO_PuPd,GPIO_Label
PE5.GPIO_Label=P1_RIGHT
PE5.GPIO_PuPd=GPIO_PULLUP
PE5.Signal=GPIO_Input
PE6.GPIOParameters=GPIO_PuPd,GPIO_Label
PE6.GPIO_Label=P1_A
PE6.GPIO_PuPd=GPIO_PULLUP
PE6.Signal=GPIO_Input
PE7.GPIOParameters=GPIO_PuPd,GPIO_Label
PE7.GPIO_Label=P1_B
PE7.GPIO_PuPd=GPIO_PULLUP
PE7.Signal=GPIO_Input
PE8.GPIOParameters=GPIO_PuPd,GPIO_Label
PE8.GPIO_Label=P2_UP
PE8.GPIO_PuPd=GPIO_PULLUP
PE8.Signal=GPIO_Input
PE9.GPIOParameters=GPIO_PuPd,GPIO_Label
PE9.GPIO_Label=P2_DOWN
PE9.GPIO_PuPd=GPIO_PULLUP
PE9.Signal=GPIO_Input
PH0-OSC_IN\ (PH0).Mode=HSE-External-Oscillator
PH0-OSC_IN\ (PH0).Signal=RCC_OSC_IN
PH1-OSC_OUT\ (PH1).Mode=HSE-External-Oscillator
PH1-OSC_OUT\ (PH1).Signal=RCC_OSC_OUT
RCC.HSE_VALUE=16000000
RCC.SYSCLKFreq_VALUE=160000000
RCC.SYSCLKSource=RCC_SYSCLKSOURCE_PLLCLK
board=custom

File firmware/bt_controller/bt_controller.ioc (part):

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Mcu.Name=STM32WB1MMCHx
Mcu.Package=LGA77
Mcu.UserName=STM32WB1MMCHx
PA0.GPIOParameters=GPIO_PuPd,GPIO_Label
PA0.GPIO_Label=BTN_UP
PA0.GPIO_PuPd=GPIO_PULLUP
PA0.Signal=GPIO_Input
PA13.Mode=Serial_Wire
PA13.Signal=SYS_JTMS-SWDIO
PA14.Mode=Serial_Wire
PA14.Signal=SYS_JTCK-SWCLK
PA2.GPIOParameters=GPIO_PuPd,GPIO_Label
PA2.GPIO_Label=BTN_DOWN
PA2.GPIO_PuPd=GPIO_PULLUP
PA2.Signal=GPIO_Input
PA3.GPIOParameters=GPIO_PuPd,GPIO_Label
PA3.GPIO_Label=BTN_LEFT
PA3.GPIO_PuPd=GPIO_PULLUP
PA3.Signal=GPIO_Input
PB4.GPIOParameters=GPIO_PuPd,GPIO_Label
PB4.GPIO_Label=BTN_RIGHT
PB4.GPIO_PuPd=GPIO_PULLUP
PB4.Signal=GPIO_Input
PB5.GPIOParameters=GPIO_PuPd,GPIO_Label
PB5.GPIO_Label=BTN_A
PB5.GPIO_PuPd=GPIO_PULLUP
PB5.Signal=GPIO_Input
PB6.GPIOParameters=GPIO_PuPd,GPIO_Label
PB6.GPIO_Label=BTN_B
PB6.GPIO_PuPd=GPIO_PULLUP
PB6.Signal=GPIO_Input
RCC.HSE_VALUE=32000000
RCC.SYSCLKFreq_VALUE=32000000
RCC.SYSCLKSource=RCC_SYSCLKSOURCE_HSE
board=custom
